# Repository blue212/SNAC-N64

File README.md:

# SNAC
N64 Accessory converter for MiSTer, by blue212

Serial Native Accessory Converter

SNAC adapter for N64. This board and N64 use 3v3 logic. This is a standalone board, so it's not to used with the SNAC level shifter board. You can use a short male to female usb3.0 extension cable between it and misters USER port.

It has four ports for controllers which are independently controlled in the OSD.

Rumble, transfer, controller paks, vru and microphone all supported.

-TODO 
case

-Updates

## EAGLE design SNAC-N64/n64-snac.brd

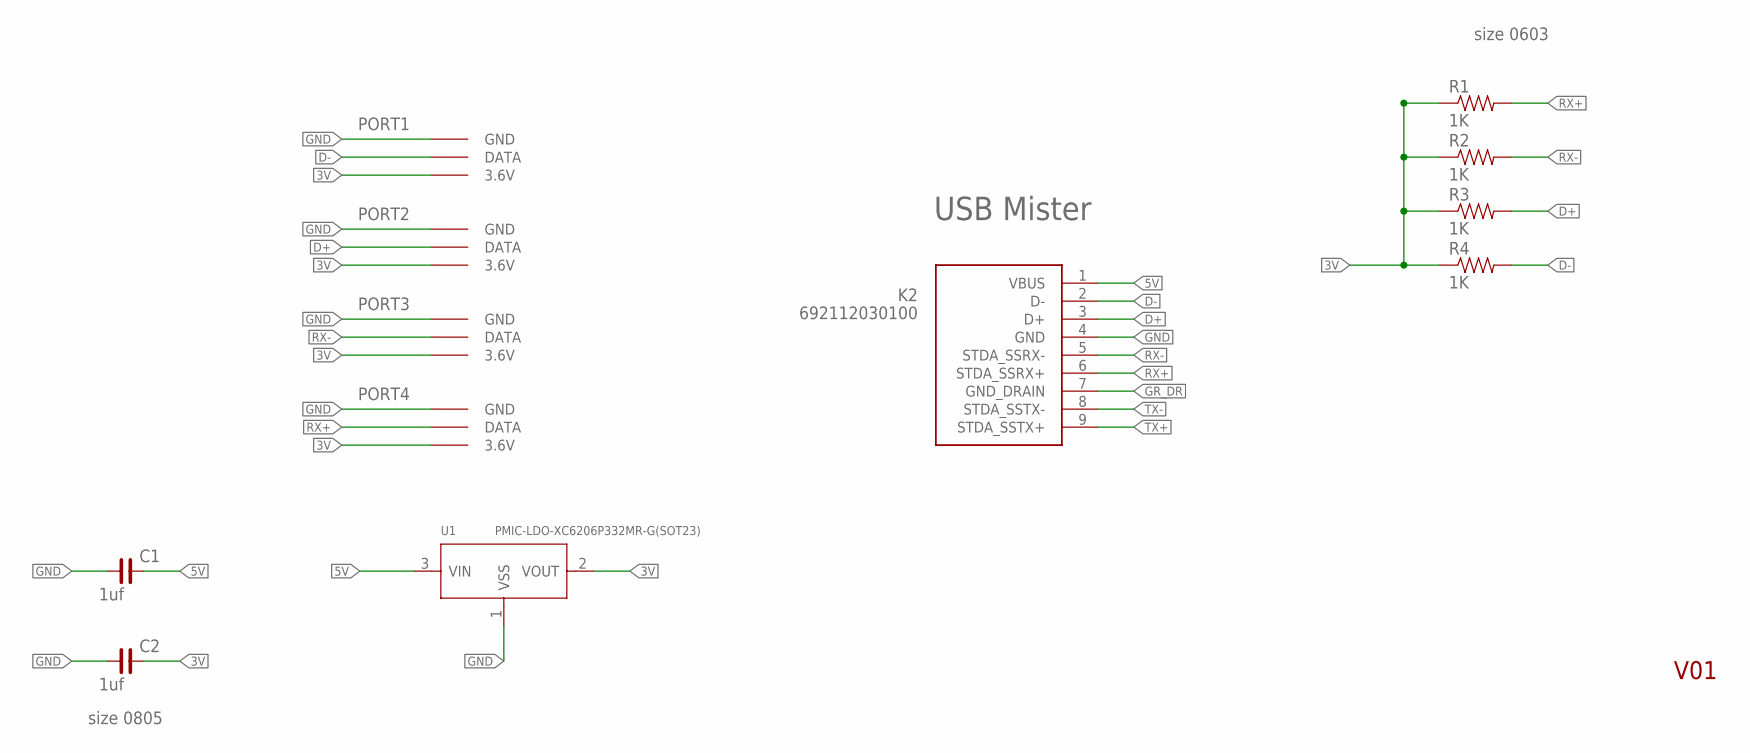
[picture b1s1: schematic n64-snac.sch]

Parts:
C1, C2: 1uf; C0805
K2: 692112030100
R1, R2, R3, R4: 1K; 0603-RES
U1: PMIC-LDO-XC6206P332MR-G(SOT23); SOT-23
U$1, U$2, U$3, U$4: N64CONN

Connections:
3V: C2.2, R1.1, R2.1, R3.1, R4.1, U1.2 (VOUT), U$1.3.6V, U$2.3.6V, U$3.3.6V, U$4.3.6V
5V: C1.2, K2.1 (VBUS), U1.3 (VIN)
D+: K2.3 (D+), R3.2, U$1.DATA
D-: K2.2 (D-), R4.2, U$3.DATA
GND: C1.1, C2.1, K2.4 (GND), U1.1 (VSS), U$1.GND, U$2.GND, U$3.GND, U$4.GND
GR_DR: K2.7 (GND_DRAIN)
RX+: K2.6 (STDA_SSRX+), R1.2, U$4.DATA
RX-: K2.5 (STDA_SSRX-), R2.2, U$2.DATA
TX+: K2.9 (STDA_SSTX+)
TX-: K2.8 (STDA_SSTX-)

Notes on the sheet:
V01
USB Mister
size 0805
size 0603
PORT1
PORT2
PORT3
PORT4

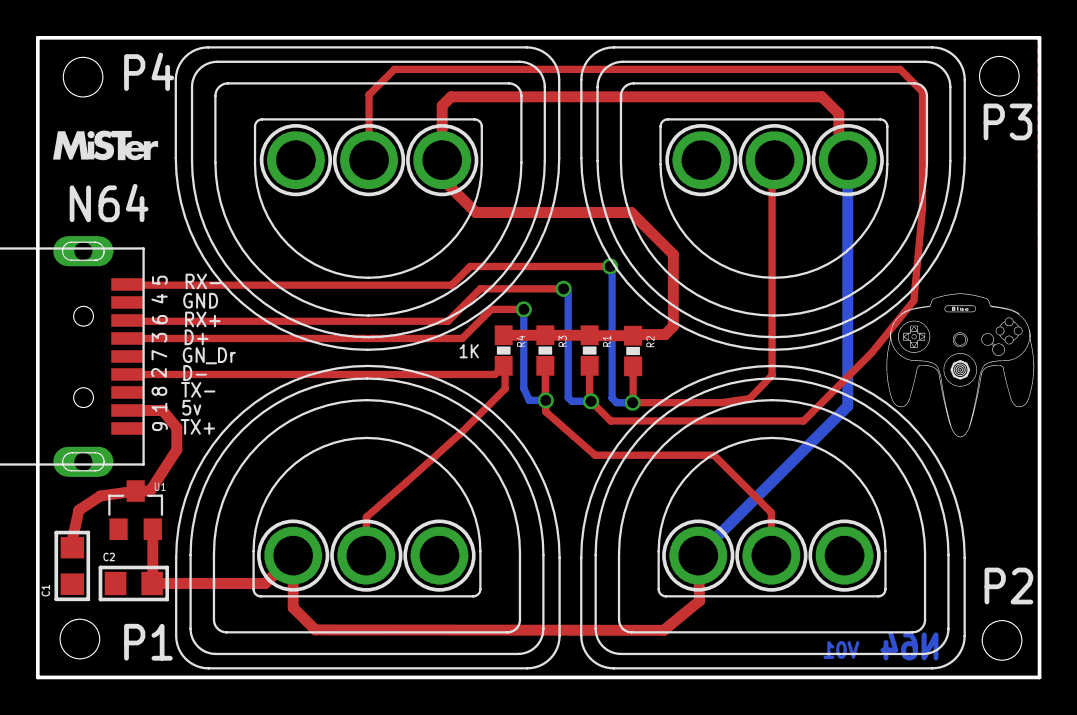
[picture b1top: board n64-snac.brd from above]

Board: 2 copper layers, 55.7 x 35.5 mm, 12 parts (0 on the bottom side), 7 nets.

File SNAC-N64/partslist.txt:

Part  Value                          Device                         Package      Description                                         
C1    1uf                            C_0805                         C0805        NON-POLARIZED CAP                                                                                                                                                                                                                                                                                                                                                                                                 
C2    1uf                            C_0805                         C0805        NON-POLARIZED CAP                                                                                                                                                                                                                                                                                                                                                                                                 
CONT1 N64                            N64                            TE_N64       Check prices    
CONT2 N64                            N64                            TE_N64       Check prices   
CONT3 N64                            N64                            TE_N64       Check prices    
CONT4 N64                            N64                            TE_N64       Check prices   
K2    692112030100                   692112030100                   692112030100 WR-COM  USB 3.0 SMT PLUG WITH CLIPTYPE A                                                                                                                                                                                                                                                                                                                                                                          
R1    1K                             RESISTOR0603-RES               0603-RES     Resistor                                                                                                                                                                                                                                                                                                                                                                                                          
R2    1K                             RESISTOR0603-RES               0603-RES     Resistor                                                                                                                                                                                                                                                                                                                                                                                                          
R3    1K                             RESISTOR0603-RES               0603-RES     Resistor                                                                                                                                                                                                                                                                                                                                                                                                          
R4    1K                             RESISTOR0603-RES               0603-RES     Resistor
U1    PMIC-LDO-XC6206P332MR-G(SOT23) PMIC-LDO-XC6206P332MR-G(SOT23) SOT-23       310030099 


alternate K2
K2       a19032000ux0260               a19032000ux0260              Uxcell

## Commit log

2023-11-23 Initial board design and files
    version 1
2024-02-07 add case

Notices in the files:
parts and their libraries:
Wuerth_Elektronik_eiCan_Communication_Co: Copyright: Würth Elektronik
rc-master-smd: Copyright (C) 2007, Bob Starr
SparkFun: Licensing: CC v3.0 Share-Alike You are welcome to use this library for commercial purposes.
